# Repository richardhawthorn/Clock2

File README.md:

### Description

PCB and Arduino code for a basic clock

### Features

- 4 character 7-segment LED display
- ATMEGA328P with Arduino boot-loader
- 5V operation @ 16Mhz
- DS1307 battery backed clock
- 2x buttons to update minutes and seconds
- Mini USB power connector
- FTDI programming port
- Completely through hole design

### License

This work is licensed under a Creative Commons Attribution-ShareAlike 4.0 International License.

<br />
Designed by <a xmlns:cc="http://creativecommons.org/ns#" href="http://www.richardhawthorn.com" property="cc:attributionName" rel="cc:attributionURL" target="_blank">Richard Hawthorn</a><br />
<a rel="license" href="http://creativecommons.org/licenses/by-sa/4.0/" target="_blank">View License</a>

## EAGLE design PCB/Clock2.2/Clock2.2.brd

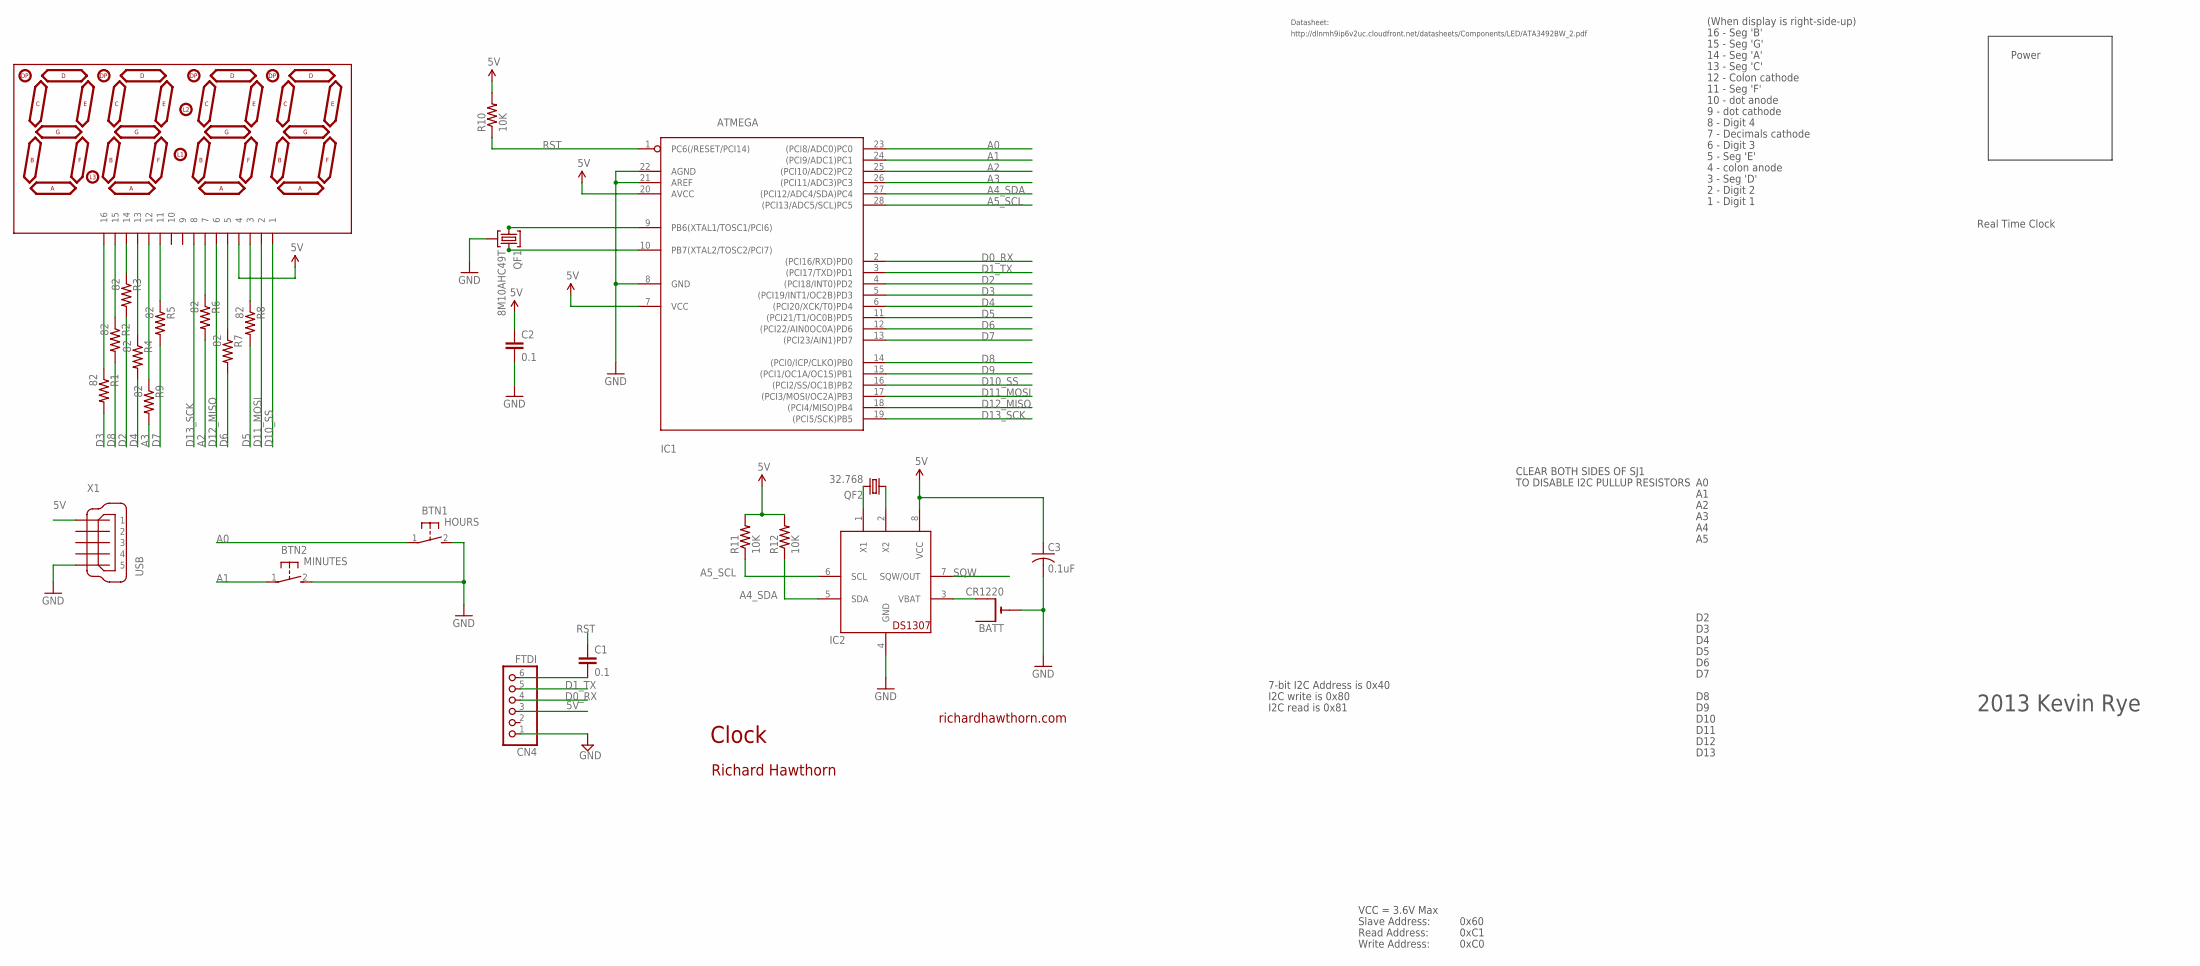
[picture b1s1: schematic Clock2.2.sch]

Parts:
BATT: CR1220; CR1220-SMD
BTN1: HOURS; DTS-3
BTN2: MINUTES; DTS-3
C1, C2: 0.1; CAP-PTH-SMALL2
C3: 0.1uF; C025-025X050
CN4: FTDI; 1X06
IC1: ATMEGA; DIL28-3-ROUND
IC2: DS1307; DIL08
LED1: 7SEG-4DIGIT; SPARKFUN_7-SEGMENT-4DIGIT
QF1: 8M10AHC49T; HC49U
QF2: 32.768; TC38H
R1, R2, R3, R4, R5, R6, R7, R8, R9: 82; 0204/7
R10, R11, R12: 10K; 0204/7
X1: USB; 32005-601

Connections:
5V: C2.1, C3.1, CN4.3, IC1.7 (VCC), IC1.20 (AVCC), IC2.8 (VCC), LED1.4, R10.2, R11.2, R12.2, X1.1
A0: BTN1.1, IC1.23 ((PCI8/ADC0)PC0)
A1: BTN2.1, IC1.24 ((PCI9/ADC1)PC1)
A2: IC1.25 ((PCI10/ADC2)PC2), R6.2
A3: IC1.26 ((PCI11/ADC3)PC3), R9.2
A4_SDA: IC1.27 ((PCI12/ADC4/SDA)PC4), IC2.5 (SDA), R12.1
A5_SCL: IC1.28 ((PCI13/ADC5/SCL)PC5), IC2.6 (SCL), R11.1
D0_RX: CN4.4, IC1.2 ((PCI16/RXD)PD0)
D1_TX: CN4.5, IC1.3 ((PCI17/TXD)PD1)
D2: IC1.4 ((PCI18/INT0)PD2), R3.2
D3: IC1.5 ((PCI19/INT1/OC2B)PD3), R1.2
D4: IC1.6 ((PCI20/XCK/T0)PD4), R4.2
D5: IC1.11 ((PCI21/T1/OC0B)PD5), R8.2
D6: IC1.12 ((PCI22/AIN0OC0A)PD6), R7.2
D7: IC1.13 ((PCI23/AIN1)PD7), R5.2
D8: IC1.14 ((PCI0/ICP/CLKO)PB0), R2.2
D9: IC1.15 ((PCI1/OC1A/OC1S)PB1)
D10_SS: IC1.16 ((PCI2/SS/OC1B)PB2), LED1.1
D11_MOSI: IC1.17 ((PCI3/MOSI/OC2A)PB3), LED1.2
D12_MISO: IC1.18 ((PCI4/MISO)PB4), LED1.6
D13_SCK: IC1.19 ((PCI5/SCK)PB5), LED1.8
GND: BATT.-, BTN1.2, BTN2.2, C2.2, C3.2, CN4.1, IC1.8 (GND), IC1.21 (AREF), IC1.22 (AGND), IC2.4 (GND), QF1.2, X1.5
unnamed: BATT.+$2 (+1), IC2.3 (VBAT)
unnamed: LED1.16, R1.1
unnamed: LED1.15, R2.1
unnamed: LED1.12, R9.1
unnamed: LED1.7, R6.1
unnamed: IC2.1 (X1), QF2.2
unnamed: IC2.2 (X2), QF2.1
unnamed: IC1.9 (PB6(XTAL1/TOSC1/PCI6)), QF1.1
unnamed: C1.2, CN4.6
unnamed: LED1.13, R4.1
unnamed: LED1.14, R3.1
unnamed: LED1.11, R5.1
unnamed: IC1.10 (PB7(XTAL2/TOSC2/PCI7)), QF1.3
unnamed: LED1.5, R7.1
unnamed: LED1.3, R8.1
RST: C1.1, IC1.1 (PC6(/RESET/PCI14)), R10.1
SQW: IC2.7 (SQW/OUT)

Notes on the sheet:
Clock
richardhawthorn.com
Richard Hawthorn
CLEAR BOTH SIDES OF SJ1
TO DISABLE I2C PULLUP RESISTORS
7-bit I2C Address is 0x40
I2C write is 0x80
I2C read is 0x81
VCC = 3.6V Max
Read Address:
Write Address:
Slave Address:
0x60
0xC1
0xC0
14 - Seg 'A'
13 - Seg 'C'
12 - Colon cathode
11 - Seg 'F'
10 - dot anode
9 - dot cathode
8 - Digit 4
7 - Decimals cathode
6 - Digit 3
5 - Seg 'E'
4 - colon anode
3 - Seg 'D'
2 - Digit 2
Real Time Clock
1 - Digit 1
15 - Seg 'G'
16 - Seg 'B'
D10
D11
D12
D13
http://dlnmh9ip6v2uc.cloudfront.net/datasheets/Components/LED/ATA3492BW_2.pdf
Datasheet:
Power
(When display is right-side-up)

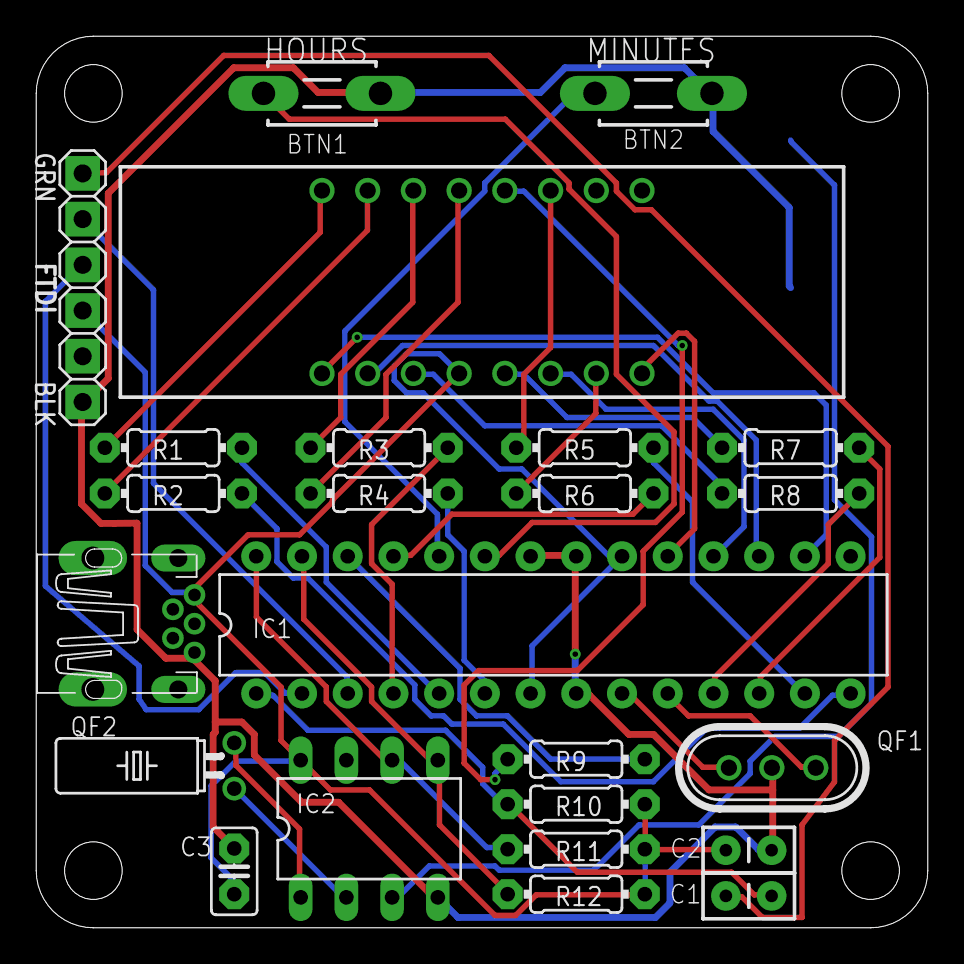
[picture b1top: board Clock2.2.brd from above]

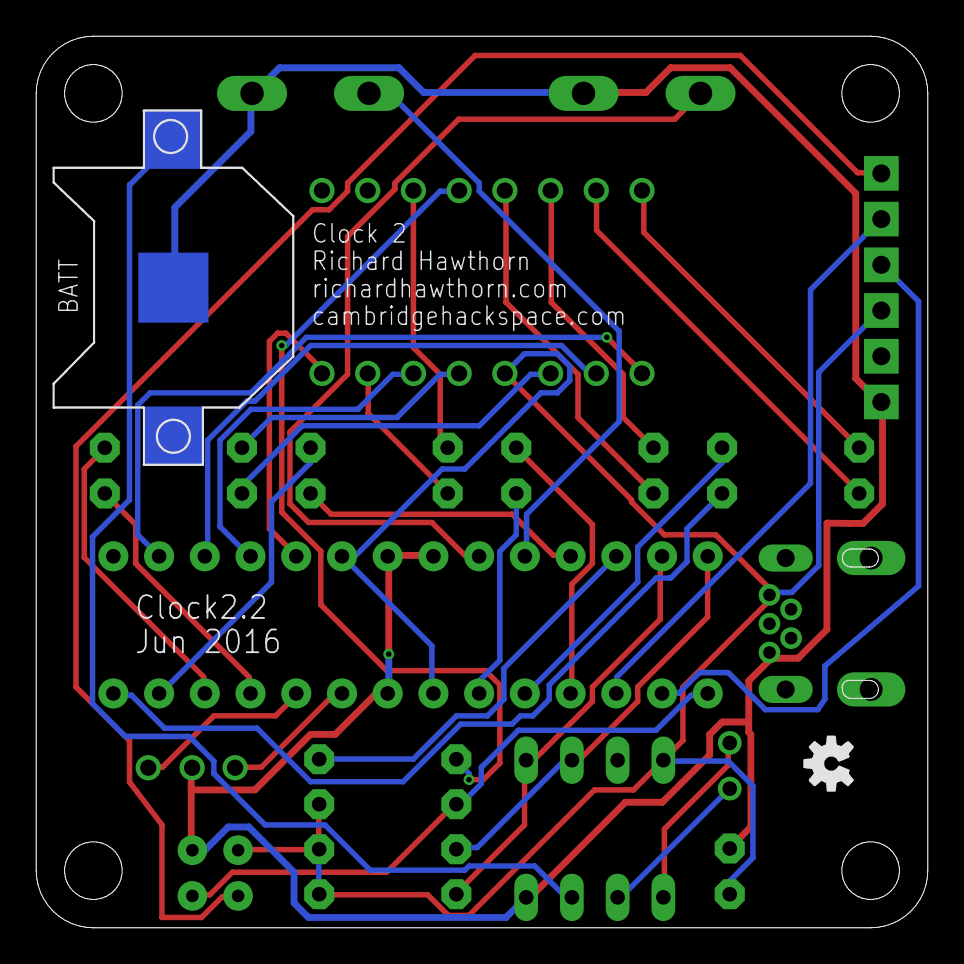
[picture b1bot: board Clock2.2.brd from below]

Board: 2 copper layers, 49.5 x 49.5 mm, 26 parts (2 on the bottom side), 37 nets.

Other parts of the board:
U$3: OSHW-LOGO-S

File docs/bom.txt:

Qty Value       Device                       Package                   Parts                              Description                                    
2   0.1uf       CAP                          CAP-PTH-SMALL             C1, C2, C3                         Capacitor                                                                                                         
3   10K         Resistor                     0204/7                    R10, R11, R12                      Resistor                                                
1   32.768      CRYTALTC38H                  TC38H                     QF2                                Crystal                                                                   
1   7SEG-4DIGIT 7SEG-4DIGIT                  7-SEGMENT-4DIGIT          LED1                               7 Segment LED                                                                          
9   82r         Resistor                     0204/7                    R1, R2, R3, R4, R5, R6, R7, R8, R9 Resistor                                               
1   16Mhz	 16Mhz Crystal                HC49U                     QF1                                Crystal                      
1   ATMEGA328P  ATMEGA328P                   DIL28-3-ROUND             IC1                                Microcontroller                                                           
1   CR1220      CR1220SMT                    CR1220-SMD                BATT                               Battery clip                            
1   DS1307      DS1307                       DIL08                     IC2                                Calendar                                                                    
1   FTDI        PINHD-1X6                    1X06                      CN4                                Pin Header                                                                
1   HOURS       DTS-3                        DTS-3                     BTN1                               Button                                                                          
1   MINUTES     DTS-3                        DTS-3                     BTN2                               Button                                                                          
1   USB         MINI-USB		       32005-601                 X1                                 USB socket

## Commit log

2016-03-29 add design files
2016-03-29 add images
2016-04-15 add bom
2016-04-15 add instructions
2016-11-08 Adding v2 of the pcb
2016-11-10 add code reference

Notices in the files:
parts and their libraries:
SparkFun-Aesthetics: Licensing: CC v3.0 Share-Alike You are welcome to use this library for commercial purposes.
